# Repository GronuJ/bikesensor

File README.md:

# bikesensor 🚲📡

**A standalone, low-cost, pure IoT hardware and software mapping pipeline for geo-tagged bike vibration and road-quality analysis.**

`bikesensor` turns an ESP32-C3 SuperMini, an MPU-6050 IMU, a NEO-6M GPS, and an SPI MicroSD card module into a standalone, battery-powered mapping box. 

When you ride, the device autonomously records high-frequency (200 Hz) vertical accelerometer vibrations and sparse (1 Hz) GPS coordinate ticks into unified local CSV log files on the SD card. When you return home, the device connects to your home Wi-Fi and uploads all offline ride CSVs over HTTPS to [kiel.earth](https://kiel.earth), where the rides are stored, processed and mapped. That website lives in its own repository; this one holds the firmware, the carrier PCB and the enclosure.

An iPhone can do the same job: [`ios/`](ios/README.md) is a small SwiftUI app that records a ride with the phone on the handlebar, writes the same CSV and posts it to the same endpoint.

---

## ⚠️ Project status

* **The custom PCB has been ordered** (38.74 × 114.47 mm, `production/bikesensor.zip`) but not assembled. Its ESP32 headers were routed against the wrong SuperMini pinout, so every signal lands on a different GPIO than the hand-wired prototype used. The default firmware build is remapped to match the board; the battery sense needs one bodge wire during assembly, and the module must be mounted face down. Details in `custom_pcb/PIN_VERIFICATION.md`.
* **The hardware has never produced a real ride.** Every figure produced so far comes from synthetic signals.

---

## 📸 Hardware Showcase

Below is the completed physical system mounted on a custom 3D-printed handlebar enclosure and its 3D modeling design:

| Physical System | 3D Printed Enclosure Design |
| :---: | :---: |
|  |  |

---

## 1. System Architecture

```mermaid
flowchart TD
    subgraph Riding [1. Outdoor Bike Ride]
        ESP[ESP32-C3 SuperMini]
        IMU[MPU-6050 Accelerometer 200Hz] --> ESP
        GPS[NEO-6M GPS Module 1Hz] --> ESP
        ESP -->|Log unified CSV| SD[(SPI MicroSD Card)]
    end

    subgraph Home [2. Arrival Home & Wi-Fi Sync]
        ESP_H[ESP32-C3 Home Mode] -->|Connects to home Wi-Fi| Router((Home Router))
        SD -->|Stream CSVs over HTTPS POST| ESP_H
        ESP_H -->|/api/bike/ingest| Site[kiel.earth]
        Site -->|2xx: file is stored| ESP_H
        ESP_H -->|Delete uploaded file| SD
    end
```

---

## 2. Hardware Wiring & Custom PCB Carrier

The hardware operates on **3.3V logic** for standard communication and SD logging, driven by a Wemos D1 Mini TP5400 Battery Shield. 

Here is the physical wiring diagram for our custom carrier board:

### Schematic

R3 (10 kΩ) pulls `SPI_CS` to `+3V3`, keeping the card deselected while the ESP32 boots. The schematic's ESP32 connectors are generic sockets, so it does not show which GPIO each net reaches; the table below does.

### Board

The carrier is 38.74 × 114.47 mm, 2-layer, all through-hole. Every connected pin carries a silkscreen signal name — `GTX`/`GRX` are the GPS UART, `DTX`/`DRX` the debug UART, and `ADC` the battery divider.

### Pin Map Table:

GPIOs are for the carrier PCB (default firmware build). The hand-wired prototype used different ones — `pio run -d firmware -e handwired`.

| Peripheral | Connection | Pin | Notes |
| :--- | :--- | :--- | :--- |
| **MPU-6050 (I2C)** | SDA | **GPIO 1** | J1.7, shared I2C bus |
| | SCL | **GPIO 2** | J1.6. Strapping pin, held high by the GY-521's pull-ups |
| | VCC / GND | **3V3 / GND** | Powered by system 3.3V rail |
| **MicroSD (SPI)** | CS | **GPIO 7** | J2.3, R3 pull-up |
| | MOSI | **GPIO 6** | J2.2 |
| | SCK | **GPIO 5** | J2.1 |
| | MISO | **GPIO 0** | J1.8 |
| | VCC / GND | **3V3 / GND** | Powered by system 3.3V rail |
| **NEO-6M (UART1)** | TX / RX | **GPIO 8 / GPIO 21** | J2.4 / J2.8. Firmware detects which one the GPS transmits on |
| | VCC / GND | **5V / GND** | Powered by 5V boost output |
| **Wemos Battery Shield** | 5V Out | **J7 Pin 8** | Boosted 5.0V output |
| | GND | **J7 Pin 7** | System Ground |
| **SPDT Slide Switch (SW1)** | In / Out | **In Series** | Connected between `J7 Pin 8` (5V out) and `5V` net (ESP32 5V pin). Completely cuts off system power while preserving USB charging. |
| **Voltage Divider (R1, R2, C3)** | Junction | **GPIO 3** | Routed to J2.5 = GPIO 9, which has no ADC; reaches GPIO 3 only via the bodge wire in `PIN_VERIFICATION.md`. **R1 (100kΩ)** and **R2 (100kΩ)** divide raw battery voltage in half (`4.2V -> 2.1V`) for safe ADC reading. **C3 (100nF)** in parallel with R2 filters noise. |
| **Decoupling Caps (C1, C2)** | Parallel | **3V3 / GND** | **C1 (47µF radial; 10µF fits but is marginal)** and **C2 (100nF ceramic)** placed in parallel next to the MicroSD socket prevent write-cycle voltage sags. |

---

## 3. Firmwares (PlatformIO)

The firmware resides in `firmware/bikesensor/bikesensor.ino` and compiles out-of-the-box.

### Secure Credentials (Git-Ignored)
To protect your home Wi-Fi passwords from being committed to Git, create a file named `private_credentials.h` inside `firmware/bikesensor/`:
```cpp
#pragma once
#define WIFI_SSID "YourHomeSSID"
#define WIFI_PASS "YourHomePassword"
#define SERVER_HOST "kiel.earth"
#define SERVER_PORT 443
#define SERVER_UPLOAD_PATH "/api/bike/ingest"
#define DEVICE_TOKEN "your-device-token"   // sent as: Authorization: Bearer <token>
```
The firmware preprocessor will automatically detect and include this file during compile, keeping your passwords safe and isolated in your local workspace.

### Compilation Commands:
```bash
pio run -d firmware              # Build firmware binary
pio run -d firmware -t upload    # Flash to ESP32-C3 (Serial port is auto-detected)
pio device monitor -b 115200     # Real-time console debugger
```

---

## 4. Device-to-Server Interface

The logging box talks to the website over a single HTTPS endpoint.

### 4.1 CSV Log Data Format
When writing to the MicroSD card, the device registers data in a unified, comma-separated format:
```csv
millis,ax,ay,az,lat,lon,ele,speed_kmh,battery_pct,gps_time
```
*   `millis`: Relative milliseconds from ESP32 boot (used to align high-frequency vibration data).
*   `ax,ay,az`: Raw vertical/lateral/longitudinal accelerometer values (the ±4 g scale, `1/8192`, is applied on the website, not on the device).
*   `lat,lon,ele,speed_kmh`: GPS coordinate details.
*   `battery_pct`: Divided battery measurement (`0 - 100%`) read from `GPIO 3` on the carrier PCB (`GPIO 0` on the hand-wired prototype).
*   `gps_time`: GPS UTC timestamp (used as a clock reference).

### 4.2 Wireless Sync Protocol
When the ESP32-C3 boots in Wi-Fi sync mode upon returning home, it uploads every ride file on the SD card, one HTTPS request each:

*   **HTTP Method:** `POST`
*   **Request URL:** `https://kiel.earth/api/bike/ingest` (set by `SERVER_HOST` / `SERVER_UPLOAD_PATH`)
*   **Request Headers:** `Content-Type: text/csv`, `Authorization: Bearer <DEVICE_TOKEN>`, `X-Ride-Id: <filename without .csv>`
*   **Request Body:** the raw CSV file.

The device deletes a file from the SD card only after a 2xx response. On a timeout, TLS failure or any other status it keeps the file and retries on the next sync.

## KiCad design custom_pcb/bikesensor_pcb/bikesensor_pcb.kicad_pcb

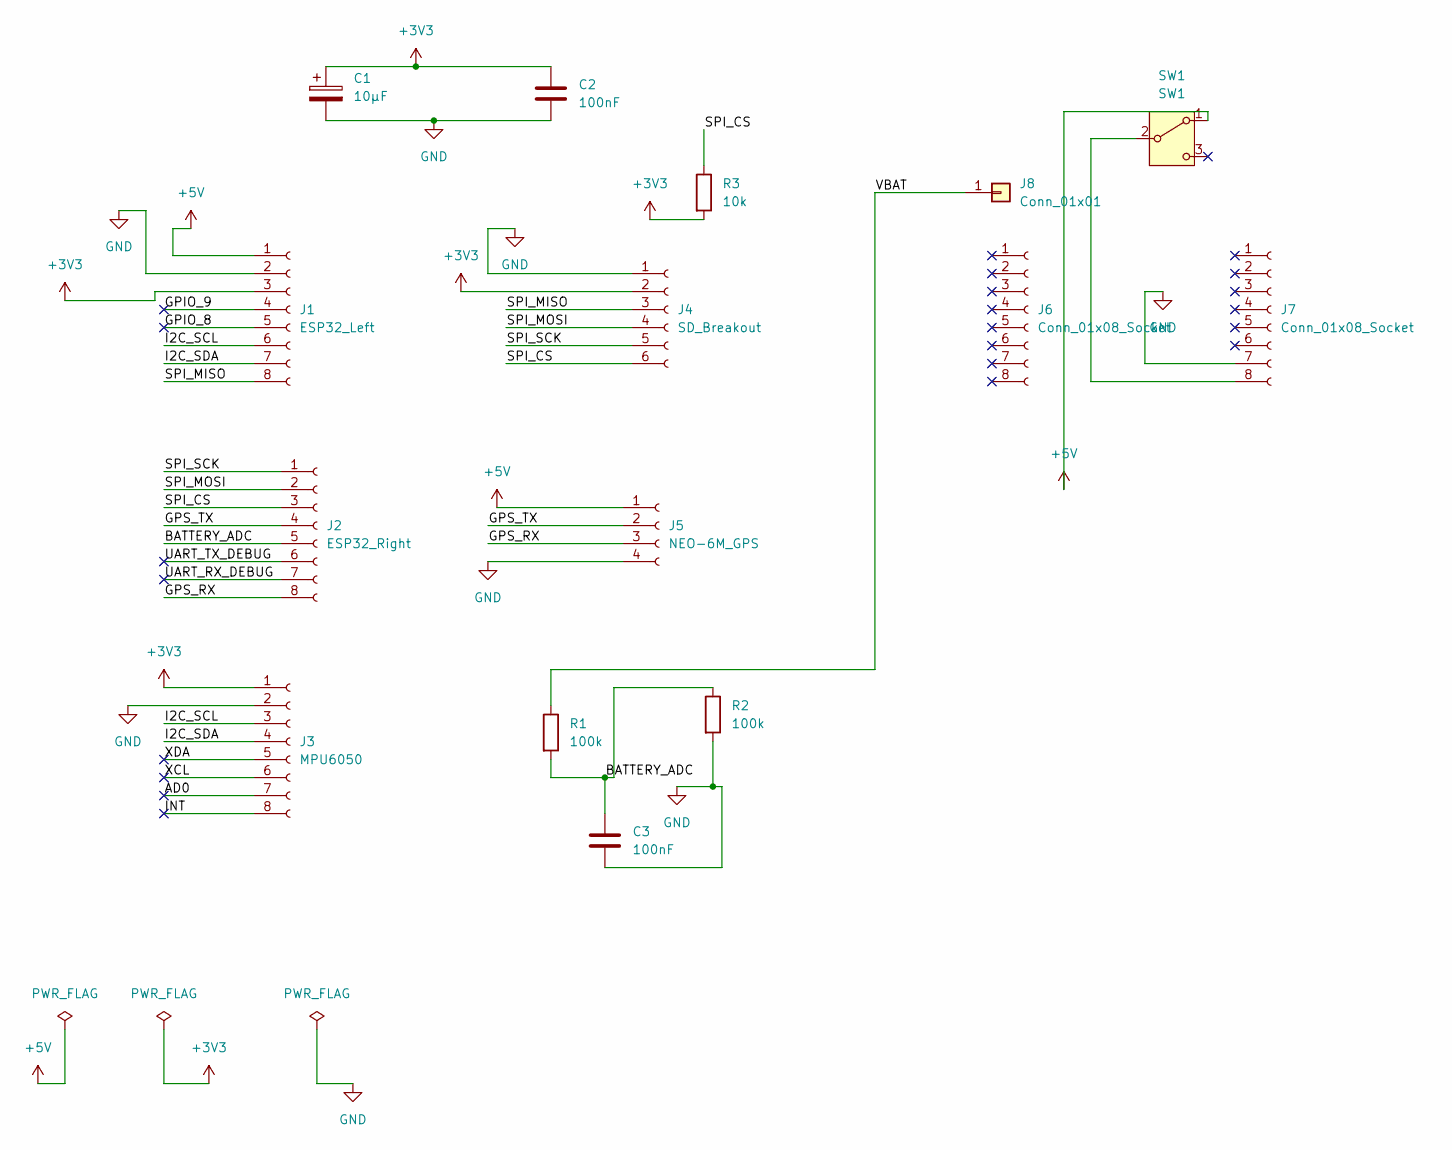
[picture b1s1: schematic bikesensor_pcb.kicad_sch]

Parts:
C1: 10µF; CP_Radial_D5.0mm_P2.00mm
C2, C3: 100nF; C_Disc_D5.0mm_W2.5mm_P5.00mm
J1: ESP32_Left; PinSocket_1x08_P2.54mm_Vertical
J2: ESP32_Right; PinSocket_1x08_P2.54mm_Vertical
J3: MPU6050; PinSocket_1x08_P2.54mm_Vertical
J4: SD_Breakout; PinSocket_1x06_P2.54mm_Vertical
J5: NEO-6M_GPS; PinSocket_1x04_P2.54mm_Vertical
J6, J7: Conn_01x08_Socket; PinSocket_1x08_P2.54mm_Vertical
J8: Conn_01x01; PinSocket_1x01_P2.54mm_Vertical
R1, R2: 100k; R_Axial_DIN0207_L6.3mm_D2.5mm_P7.62mm_Horizontal
R3: 10k; R_Axial_DIN0207_L6.3mm_D2.5mm_P7.62mm_Horizontal
SW1: SW1; SW_Slide_SPDT_Straight_CK_OS102011MS2Q

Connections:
+3V3: C1.1, C2.1, J1.3, J3.1, J4.2, R3.2
+5V: J1.1, J5.1, SW1.1 (A)
/AD0: J3.7
/BATTERY_ADC: C3.1, J2.5, R1.2, R2.1
/GPIO_8: J1.5
/GPIO_9: J1.4
/GPS_RX: J2.8, J5.3
/GPS_TX: J2.4, J5.2
/I2C_SCL: J1.6, J3.3
/I2C_SDA: J1.7, J3.4
/INT: J3.8
/SPI_CS: J2.3, J4.6, R3.1
/SPI_MISO: J1.8, J4.3
/SPI_MOSI: J2.2, J4.4
/SPI_SCK: J2.1, J4.5
/UART_RX_DEBUG: J2.7
/UART_TX_DEBUG: J2.6
/VBAT: J8.1 (Pin_1_1), R1.1
/XCL: J3.6
/XDA: J3.5
GND: C1.2, C2.2, C3.2, J1.2, J3.2, J4.1, J5.4, J7.7, R2.2
unnamed: J7.8, SW1.2 (B)

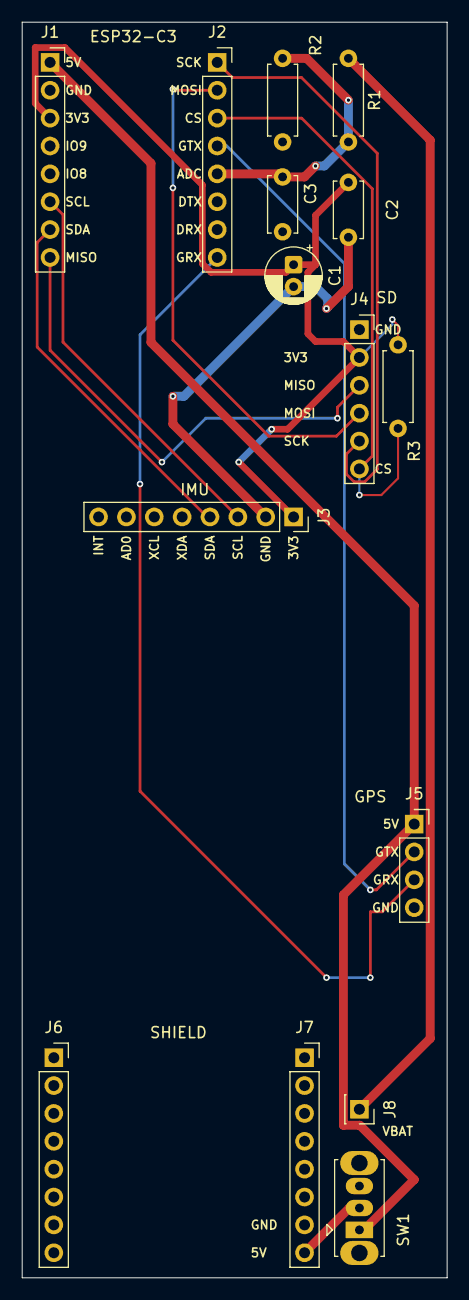
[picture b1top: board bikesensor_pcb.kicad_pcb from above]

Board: 2 copper layers, 38.7 x 114.5 mm, 15 parts (0 on the bottom side), 14 nets.

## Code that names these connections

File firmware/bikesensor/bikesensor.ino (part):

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// firmware absorbs it; only the battery ADC needed a bodge.
// See custom_pcb/PIN_VERIFICATION.md.
#ifdef BIKESENSOR_HANDWIRED
static constexpr uint8_t PIN_SPI_SCK  = 4;
static constexpr uint8_t PIN_SPI_MISO = 5;
static constexpr uint8_t PIN_SPI_MOSI = 3;
static constexpr uint8_t PIN_SPI_CS   = 2;
static constexpr uint8_t PIN_I2C_SDA  = 6;
static constexpr uint8_t PIN_I2C_SCL  = 7;
// The two pins wired to the GPS UART. Which one carries the GPS's TX is
// detected at boot, since breakouts ship with either header order.
static constexpr uint8_t PIN_GPS_A    = 10;
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static constexpr uint8_t PIN_BATTERY  = 0;
static constexpr int8_t  PIN_LED      = 8;  // onboard blue LED, active-low
#else
static constexpr uint8_t PIN_SPI_SCK  = 5;  // J2.1
static constexpr uint8_t PIN_SPI_MISO = 0;  // J1.8
static constexpr uint8_t PIN_SPI_MOSI = 6;  // J2.2
static constexpr uint8_t PIN_SPI_CS   = 7;  // J2.3, R3 pull-up
static constexpr uint8_t PIN_I2C_SDA  = 1;  // J1.7
static constexpr uint8_t PIN_I2C_SCL  = 2;  // J1.6
static constexpr uint8_t PIN_GPS_A    = 21; // J2.8 -> J5.3
static constexpr uint8_t PIN_GPS_B    = 8;  // J2.4 -> J5.2
// BATTERY_ADC is routed to J2.5 = GPIO9, which has no ADC. Readings are only
// real after the bodge wire moves the divider to J1.5 = GPIO3.
static constexpr uint8_t PIN_BATTERY  = 3;
static constexpr int8_t  PIN_LED      = -1; // GPIO8 carries the GPS UART here
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
// ---------- MICROSD ----------
static bool mountSd() {
  if (!SD.begin(PIN_SPI_CS)) return false;
  Serial.println("MicroSD card mounted successfully.");
  return true;
}
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
  // Nothing below hangs on missing hardware: a missing SD card or IMU is
  // retried from loop(), so reseating it recovers without a power cycle.
  SPI.begin(PIN_SPI_SCK, PIN_SPI_MISO, PIN_SPI_MOSI, PIN_SPI_CS);
  sdReady = mountSd();
  if (!sdReady) {
    Serial.println("❌ ERROR: MicroSD card mounting failed! Check the card; retrying every 5 s.");
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  gpsBegin();

  // A stuck bus must not stall the 5 ms loop for the core's 50 ms default.
  Wire.begin(PIN_I2C_SDA, PIN_I2C_SCL, 400000);
  Wire.setTimeOut(10);
  imuReady = mpuInit();
  if (!imuReady) {
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
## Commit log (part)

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2026-05-09 update BLE device name to bikesensor_vanhoge
2026-05-09 update BLE device name to bikesensor_vanhog
2026-05-09 feat: support multiple gpx/csv files and .txt extension
2026-05-09 fix: resolve ModuleNotFoundError when running merge.py directly
2026-05-09 feat: add streamlit file uploader and rename BLE device to bikesensor_jj
2026-05-09 docs: add detailed explanatory comments to codebase
2026-05-09 fix: resolve ModuleNotFoundError in dashboard
2026-05-10 feat: add max_bump_g metric and redesign dashboard layout
    - Add 25Hz Butterworth low-pass filter to extract max_bump_g (physical bump severity)
    - Redesign dashboard using tabs and columns for a professional layout
    - Add time-domain plot with filtered bump signal to local analysis
    - Set max_bump_g as the default map metric
2026-05-10 feat: transmit and log battery percentage via BLE
    - Read analog pin to calculate battery percentage in ESP32 firmware
    - Include battery level in the SYNC packet payload
    - Update Python parser to extract and display battery statistics
2026-05-10 updated battery status readings
2026-05-10 feat: add battery metrics to data pipeline and dashboard
    - Interpolate battery percentage across IMU samples
    - Include battery level in STFT windows
    - Display start/end battery levels on the Streamlit dashboard
    - Remove demo data generation script
    - Update README.md to reflect new battery tracking and dashboard data ingestion features
2026-05-10 fix: handle android lightblue formats and truncated ble packets
    - Fix datetime parsing in `lightblue_parse.py` to support Android exports containing GMT offsets.
    - Modify DATA packet parser to handle truncated BLE payloads (extracting as many full samples as possible).
    - Bypass the 25Hz low-pass Butterworth filter in `analysis.py` and `dashboard.py` if the sampling rate drops below the Nyquist requirement.
2026-05-10 added stl_files
2026-05-10 added presentation slides
2026-05-10 Cleaning up imagery
2026-05-10 updated the presentation
2026-05-11 chore: remove unnecessary files from repository
    Removed raw BLE log file, boilerplate main.py, and presentation.html to clean up the public repository.
2026-05-11 chore: untrack GEMINI.md and add to .gitignore
2026-05-27 feat: add standalone sd card and gps auto-wifi-sync logger
2026-05-27 fix: mock generator clip bounds and remove manual sidebar uploader
2026-05-27 clean: remove obsolete mobile app config from SD branch
2026-05-28 fix: correct TinyGPS speed method to kmph()
2026-05-28 fix: add charsProcessed to diagnostics
2026-05-28 chore: clean tech debt, secure private credentials, and update pure IoT documentation
2026-05-28 feat: add battery level interpolation and dashboard metrics card
2026-05-29 fix: robust filesystem synchronization and live battery logging
2026-05-29 Refactor: Add 0-byte sync guards, explicit content-length stream, and clean dashboard metrics
2026-05-29 Refactor: Completely remove mock ride generation features and UI elements
2026-05-29 feat: implement native macOS notification sync alerts
2026-05-29 style: display dashboard timestamps in local time and add (Latest) label
2026-05-29 fix: resolve timezone conversion TypeError in dashboard.py by converting to standard python datetime
2026-05-29 fix: explicitly format dashboard timestamps in Europe/Berlin local time zone
2026-05-29 fix: add format_func to display clear dropdown text labels instead of raw integers in dashboard selectbox
2026-05-29 docs: update README.md to document native macOS SSH notifications
2026-05-29 fix: restore strict GPS fixes requirement to preserve geographic data integrity
2026-05-29 feat: implement satellite atomic clock logging and smart ride start-time calculation
2026-05-29 fix: make datetime parsing and short-ride checks robust in background ingestion
2026-05-29 fix: make dashboard timestamp parsing robust with mixed formats
2026-05-29 fix: localize all displayed timestamps to Europe/Berlin timezone
2026-05-29 fix: enforce datetimes inside load_all_rides_data to prevent mixed-type sorting crash
2026-05-29 feat: add X-Axis toggle between Distance and Elapsed Time in Analytics tab
2026-05-29 style: remove all emojis and rename dashboard title to Dashboard for a clean professional look
2026-05-29 fix: dispatch background task immediately using asyncio.create_task to bypass event loop idle sleep on Pi
2026-05-29 fix zero-byte directory entry bug on battery power cycle
2026-05-29 add fail-safe afplay audio chime to macOS notifications
2026-05-29 update send_mac_notification to use launchctl asuser 501 for native focus-respecting GUI notifications
2026-05-29 add focus-respecting native macOS HTTP notification listener
2026-05-29 add non-blocking heartbeat LED blink and remove all remote notifications for security and privacy
2026-05-29 completely remove notification routing from server
2026-05-29 fix: race-free gps latch, timing jitter, robust fallback and upload timeout
2026-05-29 fix: safely handle NaN battery percent values in Streamlit metric
2026-06-10 feat: add custom pcb layout, production gerbers, and updated readme
2026-06-15 new screenshots
